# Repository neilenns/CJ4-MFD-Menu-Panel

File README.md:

# CJ4 MFD menu panel for use with MobiFlight

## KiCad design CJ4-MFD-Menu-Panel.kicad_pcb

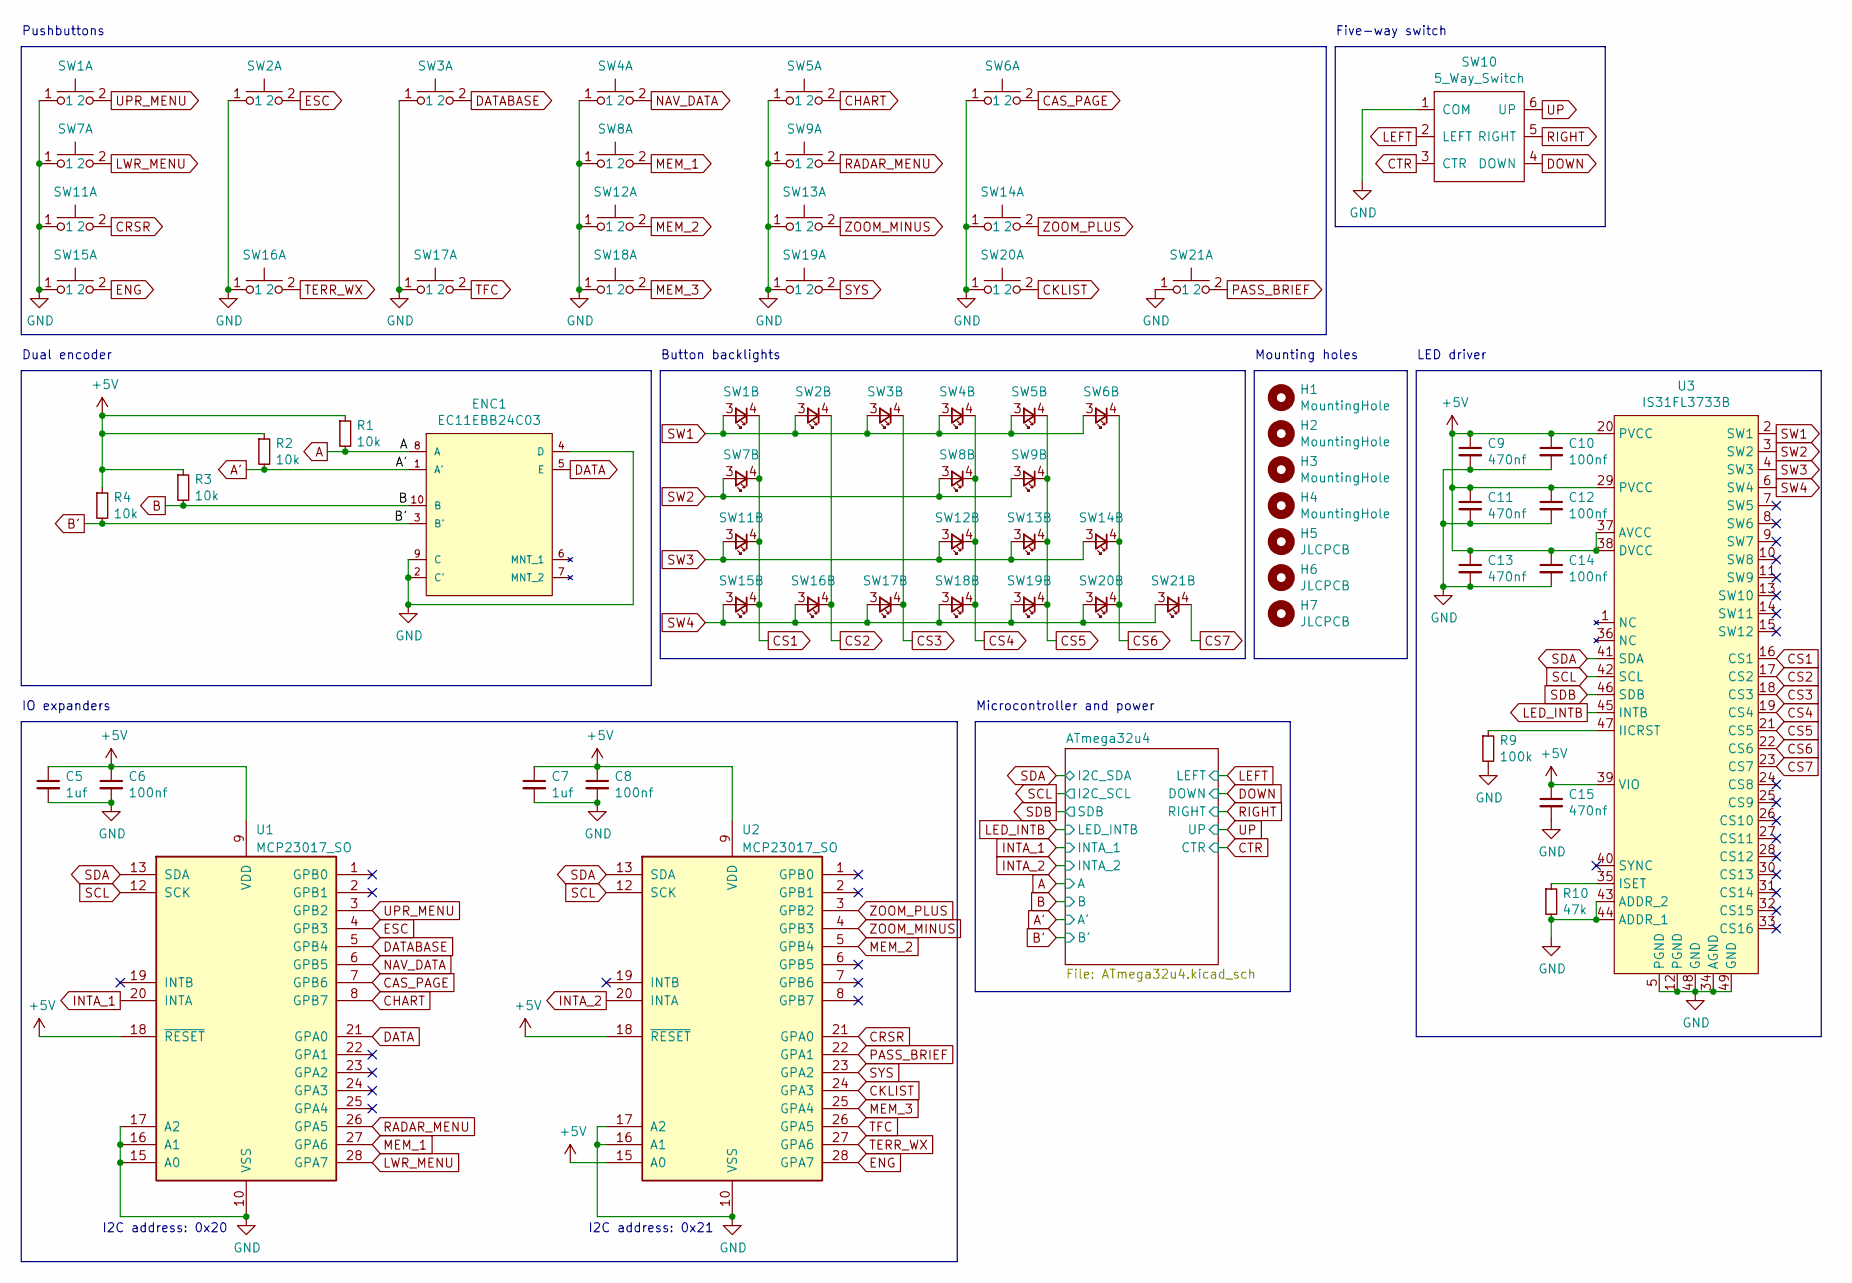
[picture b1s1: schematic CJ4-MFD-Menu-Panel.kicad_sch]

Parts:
C5, C7: 1uf; Perfect_0402; JLC 0402
C6, C8, C10, C12, C14: 100nf; Perfect_0402; JLC 0402
C9, C11, C13, C15: 470nf; Perfect_0402; JLC 0402
ENC1: EC11EBB24C03; ALPS-EC11EBB24C03-0; Rating 10mA 5VDC; mouser part number 688-EC11EBB24C03
H1, H2, H3, H4: MountingHole; MountingHole_3.2mm_M3; JLC DNP
H5, H6, H7: JLCPCB; JLCPCB_Tooling_Hole; JLC DNP
R1, R2, R3, R4: 10k; Perfect_0402; JLC 0402
R9: 100k; Perfect_0402; JLC 0402
R10: 47k; Perfect_0402; JLC 0402
SW1, SW2, SW3, SW4, SW5, SW6, SW7, SW8, SW9, SW11, SW12, SW13, SW14, SW15, SW16, SW17, SW18, SW19, SW20, SW21: SW_Push_LED; SW_PUSH_6mm; JLC DNP
SW10: 5_Way_Switch; JLC DNP
U1, U2: MCP23017_SO; SOIC-28W_7.5x17.9mm_P1.27mm; JLC DNP
U3: IS31FL3733B; TQFP-48-1EP_7x7mm_P0.5mm_EP5x5mm_ThermalVias; JLC DNP

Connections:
+5V: C5.1, C6.1, C7.1, C8.1, C9.1, C10.1, C11.1, C12.1, C13.1, C14.1, C15.1, R1.1, R2.1, R3.1, R4.1, U1.9 (VDD), U1.18 (~RESET), U2.9 (VDD), U2.15 (A0), U2.18 (~RESET), U3.20 (PVCC), U3.29 (PVCC), U3.37 (AVCC), U3.38 (DVCC), U3.39 (VIO); also elsewhere on the board
A: ENC1.8 (A), R1.2; also elsewhere on the board
A': ENC1.1 (A'), R2.2; also elsewhere on the board
B: ENC1.10 (B), R3.2; also elsewhere on the board
B': ENC1.3 (B'), R4.2; also elsewhere on the board
CAS_PAGE: SW6.2, U1.7 (GPB6)
CHART: SW5.2, U1.8 (GPB7)
CKLIST: SW20.2, U2.24 (GPA3)
CRSR: SW11.2, U2.21 (GPA0)
CS1: SW1.4, SW7.4, SW11.4, SW15.4, U3.16 (CS1)
CS2: SW2.4, SW16.4, U3.17 (CS2)
CS3: SW3.4, SW17.4, U3.18 (CS3)
CS4: SW4.4, SW8.4, SW12.4, SW18.4, U3.19 (CS4)
CS5: SW5.4, SW9.4, SW13.4, SW19.4, U3.21 (CS5)
CS6: SW6.4, SW14.4, SW20.4, U3.22 (CS6)
CS7: SW21.4, U3.23 (CS7)
CTR: SW10.3 (CTR); also elsewhere on the board
DATABASE: SW3.2, U1.5 (GPB4)
DOWN: SW10.4 (DOWN); also elsewhere on the board
ENG: SW15.2, U2.28 (GPA7)
ESC: SW2.2, U1.4 (GPB3)
E_BTN: ENC1.5 (E), U1.21 (GPA0)
GND: C5.2, C6.2, C7.2, C8.2, C9.2, C10.2, C11.2, C12.2, C13.2, C14.2, C15.2, ENC1.2 (C'), ENC1.4 (D), ENC1.9 (C), R9.2, R10.2, SW1.1, SW2.1, SW3.1, SW4.1, SW5.1, SW6.1, SW7.1, SW8.1, SW9.1, SW10.1 (COM), SW11.1, SW12.1, SW13.1, SW14.1, SW15.1, SW16.1, SW17.1, SW18.1, SW19.1, SW20.1, SW21.1, U1.10 (VSS), U1.15 (A0), U1.16 (A1), U1.17 (A2), U2.10 (VSS), U2.16 (A1), U2.17 (A2), U3.5 (PGND), U3.12 (PGND), U3.34 (AGND), U3.43 (ADDR_2), U3.44 (ADDR_1), U3.48 (GND), U3.49 (GND); also elsewhere on the board
INTA_1: U1.20 (INTA); also elsewhere on the board
INTA_2: U2.20 (INTA); also elsewhere on the board
LED_INTB: U3.45 (INTB); also elsewhere on the board
LEFT: SW10.2 (LEFT); also elsewhere on the board
LWR_MENU: SW7.2, U1.28 (GPA7)
MEM_1: SW8.2, U1.27 (GPA6)
MEM_2: SW12.2, U2.5 (GPB4)
MEM_3: SW18.2, U2.25 (GPA4)
NAV_DATA: SW4.2, U1.6 (GPB5)
unnamed: R9.1, U3.47 (IICRST)
unnamed: R10.1, U3.35 (ISET)
PASS_BRIEF: SW21.2, U2.22 (GPA1)
RADAR_MENU: SW9.2, U1.26 (GPA5)
RIGHT: SW10.5 (RIGHT); also elsewhere on the board
SCL: U1.12 (SCK), U2.12 (SCK), U3.42 (SCL); also elsewhere on the board
SDA: U1.13 (SDA), U2.13 (SDA), U3.41 (SDA); also elsewhere on the board
SDB: U3.46 (SDB); also elsewhere on the board
SW1: SW1.3, SW2.3, SW3.3, SW4.3, SW5.3, SW6.3, U3.2 (SW1)
SW2: SW7.3, SW8.3, SW9.3, U3.3 (SW2)
SW3: SW11.3, SW12.3, SW13.3, SW14.3, U3.4 (SW3)
SW4: SW15.3, SW16.3, SW17.3, SW18.3, SW19.3, SW20.3, SW21.3, U3.6 (SW4)
SYS: SW19.2, U2.23 (GPA2)
TERR_WX: SW16.2, U2.27 (GPA6)
TFC: SW17.2, U2.26 (GPA5)
UP: SW10.6 (UP); also elsewhere on the board
UPR_MENU: SW1.2, U1.3 (GPB2)
ZOOM_MINUS: SW13.2, U2.4 (GPB3)
ZOOM_PLUS: SW14.2, U2.3 (GPB2)

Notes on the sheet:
Pushbuttons
IO expanders
LED driver
Button backlights
Microcontroller and power
Five-way switch
Dual encoder
I2C address: 0x20
I2C address: 0x21
Mounting holes

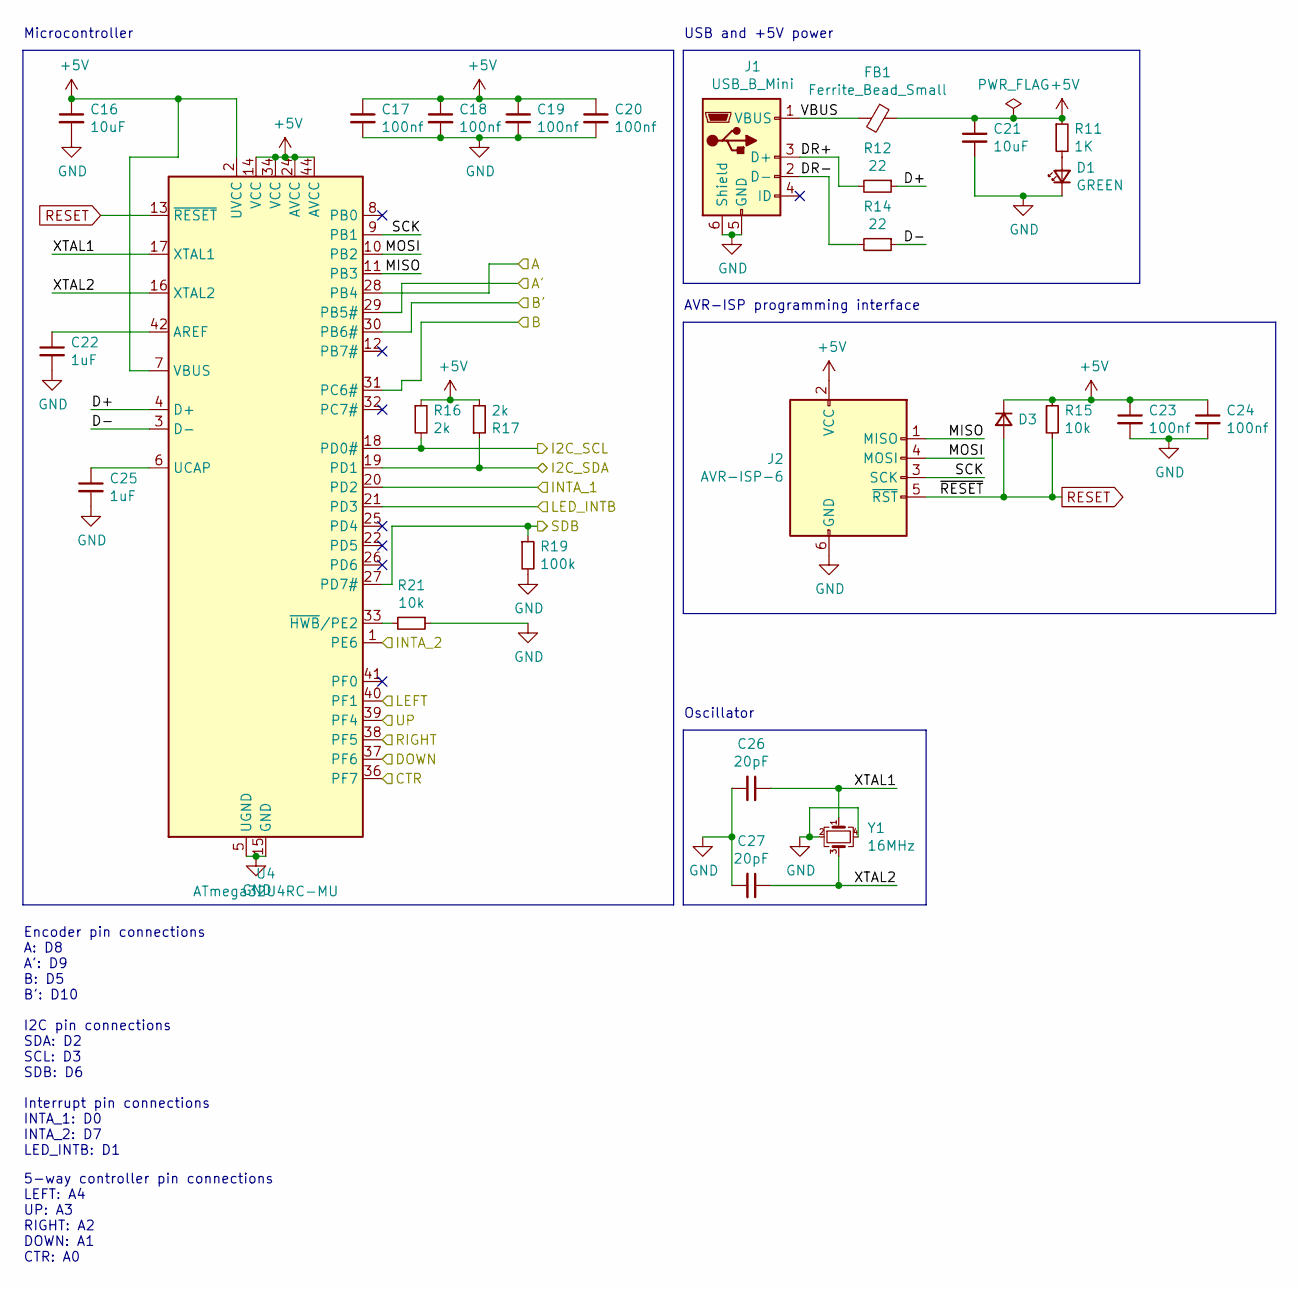
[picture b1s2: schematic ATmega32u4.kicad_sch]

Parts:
C16, C21: 10uF; Perfect_0402; JLC 0402
C17, C18, C19, C20, C23, C24: 100nf; Perfect_0402; JLC 0402
C22, C25: 1uF; Perfect_0402; JLC 0402
C26, C27: 20pF; Perfect_0402; JLC 0402
D1: GREEN; LED_0805_2012Metric_Pad1.15x1.40mm_HandSolder; JLC DNP
D3: D_Small; D_SOD-323F; JLC SOD-323F
FB1: Ferrite_Bead_Small; C_0805_2012Metric; JLC 0805
J1: USB_B_Mini; USB_B_Mini_Amphenol_UE25BE5510H; JLC DNP
J2: AVR-ISP-6; Tag-Connect_TC2030-IDC-NL_2x03_P1.27mm_Vertical; JLC DNP
R11: 1K; Perfect_0402; JLC 0402
R12, R14: 22; Perfect_0402; JLC 0402
R15, R21: 10k; Perfect_0402; JLC 0402
R16, R17: 2k; R_0805_2012Metric_Pad1.20x1.40mm_HandSolder; JLC 0805
R19: 100k; Perfect_0402; JLC 0402
U4: ATmega32U4RC-MU; QFN-44-1EP_7x7mm_P0.5mm_EP5.2x5.2mm; JLC DNP
Y1: 16MHz; Crystal_SMD_3225-4Pin_3.2x2.5mm; JLC SMD-CRY-3225_4P

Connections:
+5V: C16.1, C17.1, C18.1, C19.1, C20.1, C21.1, C23.1, C24.1, D3.1 (K), FB1.1, J2.2 (VCC), R11.1, R15.1, R16.1, R17.2, U4.2 (UVCC), U4.7 (VBUS), U4.14 (VCC), U4.24 (AVCC), U4.34 (VCC), U4.44 (AVCC); also elsewhere on the board
/ATmega32u4/D+: R12.1, U4.4 (D+)
/ATmega32u4/D-: R14.1, U4.3 (D-)
/ATmega32u4/DR+: J1.3 (D+), R12.2
/ATmega32u4/DR-: J1.2 (D-), R14.2
/ATmega32u4/MISO: J2.1 (MISO), U4.11 (PB3)
/ATmega32u4/MOSI: J2.4 (MOSI), U4.10 (PB2)
/ATmega32u4/SCK: J2.3 (SCK), U4.9 (PB1)
/ATmega32u4/VBUS: FB1.2, J1.1 (VBUS)
/ATmega32u4/XTAL1: C26.1, U4.17 (XTAL1), Y1.1
/ATmega32u4/XTAL2: C27.1, U4.16 (XTAL2), Y1.3
A: U4.28 (PB4); also elsewhere on the board
A': U4.29 (PB5#); also elsewhere on the board
B: U4.31 (PC6#); also elsewhere on the board
B': U4.30 (PB6#); also elsewhere on the board
CTR: U4.36 (PF7); also elsewhere on the board
DOWN: U4.37 (PF6); also elsewhere on the board
GND: C16.2, C17.2, C18.2, C19.2, C20.2, C21.2, C22.2, C23.2, C24.2, C25.2, C26.2, C27.2, D1.1 (K), J1.5 (GND), J1.6 (Shield), J2.6 (GND), R19.2, R21.1, U4.5 (UGND), U4.15 (GND), U4.23 (GND), U4.35 (GND), U4.43 (GND), U4.45 (GND), Y1.2, Y1.4; also elsewhere on the board
INTA_1: U4.20 (PD2); also elsewhere on the board
INTA_2: U4.1 (PE6); also elsewhere on the board
LED_INTB: U4.21 (PD3); also elsewhere on the board
LEFT: U4.40 (PF1); also elsewhere on the board
unnamed: C22.1, U4.42 (AREF)
unnamed: C25.1, U4.6 (UCAP)
unnamed: D1.2 (A), R11.2
unnamed: R21.2, U4.33 (~HWB/PE2)
RESET: D3.2 (A), J2.5 (~RST), R15.2, U4.13 (~RESET)
RIGHT: U4.38 (PF5); also elsewhere on the board
SCL: R16.2, U4.18 (PD0#); also elsewhere on the board
SDA: R17.1, U4.19 (PD1); also elsewhere on the board
SDB: R19.1, U4.27 (PD7#); also elsewhere on the board
UP: U4.39 (PF4); also elsewhere on the board

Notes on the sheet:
USB and +5V power
I2C pin connections SDA: D2 SCL: D3 SDB: D6
Encoder pin connections A: D8 A': D9 B: D5 B': D10
AVR-ISP programming interface
Microcontroller
Oscillator
5-way controller pin connections LEFT: A4 UP: A3 RIGHT: A2 DOWN: A1 CTR: A0
Interrupt pin connections INTA_1: D0 INTA_2: D7 LED_INTB: D1

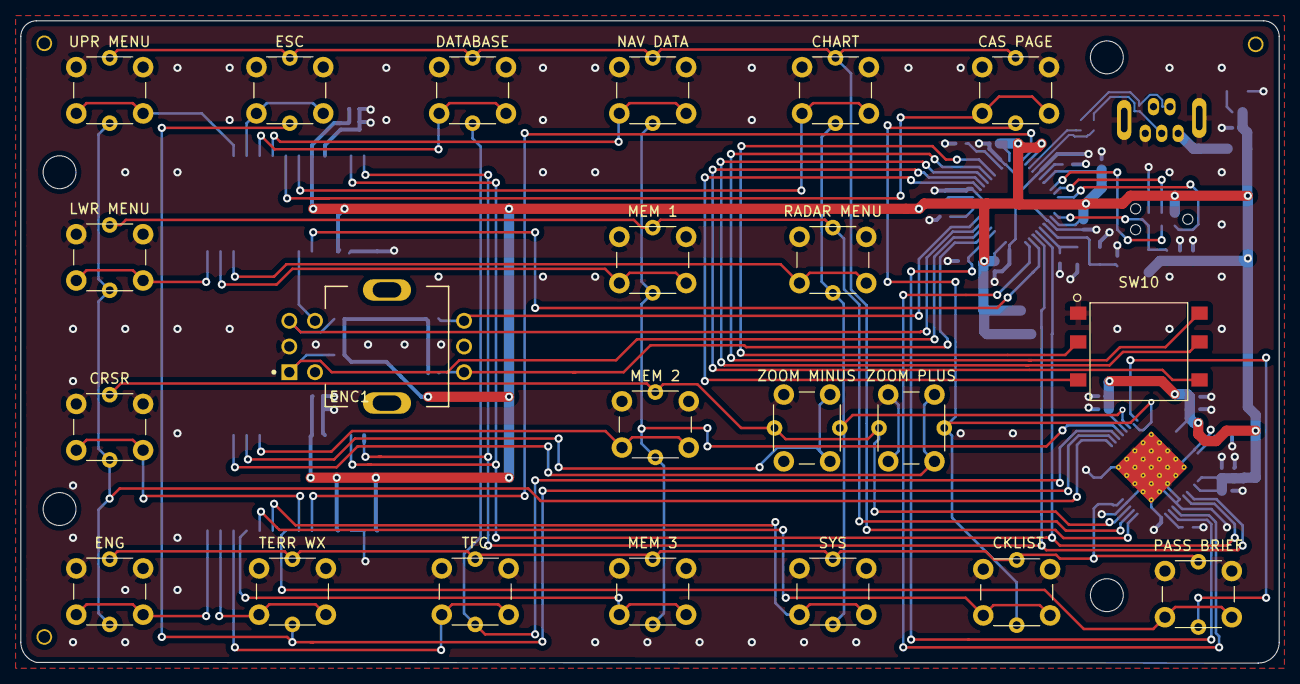
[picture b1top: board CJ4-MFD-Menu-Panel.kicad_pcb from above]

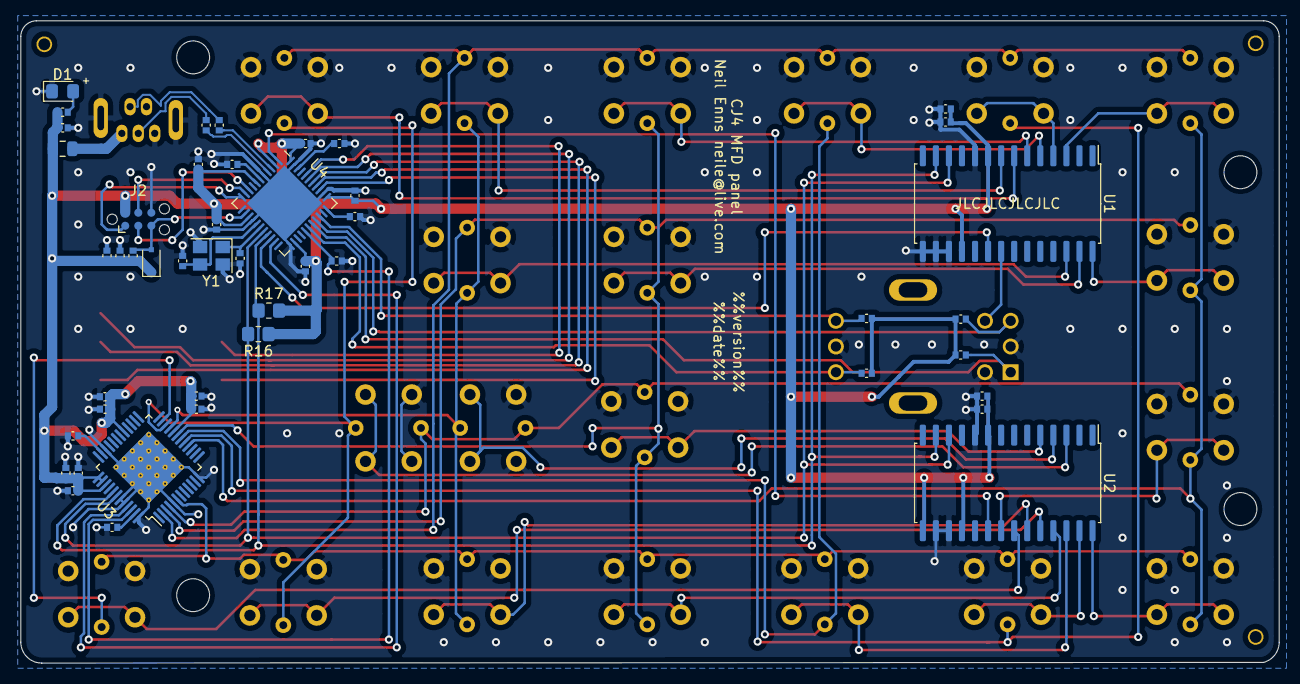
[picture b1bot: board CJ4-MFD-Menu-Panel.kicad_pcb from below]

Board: 2 copper layers, 122.4 x 62.5 mm, 76 parts (47 on the bottom side), 66 nets.

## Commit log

2021-12-01 Project creation
2021-12-01 Bunch of stuff added to the schematic
2021-12-02 Layout + PCB
2021-12-02 Switch footprint, attempt routing
2021-12-03 Footprint changes, update board size
2021-12-03 Switch to jtag
2021-12-03 ATmega32u4 layout in progress
2021-12-03 More routing. What a pain.
2021-12-06 Partiall routed but going to rip it all up and start over
2021-12-07 Fully routed and ready to go
2021-12-07 Fix footprint, via errors
2021-12-07 Clean up footprint references
2022-01-11 Miscellaneous fixes
2022-01-11 PCB generation is failing due to date replacement Fixes #11
2022-01-13 Clean up schematic Fixes #13
2022-02-06 Fix JLCPCB part assignment
2022-02-07 Ready for round two
2022-02-07 Change date format to just date, no time
2022-02-11 Rename a global label to match event name
2022-09-28 Update to KiCad 6, update 3D models
2025-02-25 Add renovate.json

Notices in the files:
CJ4-MFD-Menu-Panel.kicad_pcb:
License: MIT
